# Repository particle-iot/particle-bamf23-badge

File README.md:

# Particle Bay Area Maker Faire 2023 Water Balloon Badge 

## Our interactive game

If you stopped by the Particle booth for the 2023 Bay Area Maker Faire, spun the prize wheel, and were lucky enough to win our badge, we hope you had a blast playing! 

So, how does it work? Participants turn on their badge(s) and wait for the small LED to glow cyan, letting them know it's ready for a game match to begin. The badge has four buttons, each serving as a launcher for virtual water balloons. Each button triggers attacks with varying strengths, all determined by a virtual die roll. Players take turns launching virtual water balloons, and after an attack and counter-attack, the badges will display the result of the match automatically.  The badge lights up green for a win, red for loss, or blue for a draw.  Players engage with fellow attendees in virtual water balloon battles, roll the dice, aim for high-strength attacks, and secure their win!

Players can only battle the same player up to 10 times (after which badges win glow white to alert you of the limit), so everyone must engage with new players to climb up the leaderboard.

Pro Tip: Point the die side edges of the badges towards each other for the best results (like the video below). The max distance is 10 feet, but the closer you are, the better.

Fun fact: iPhone IR depth mapping is detrimental to gameplay functionality.  So if you are wondering why your badges seem camera shy while videoing, this is why :D

## Gameplay

## Behind the Badge

The Photon 2 based badge isn't just a fun toy. With features like a dual-row socket for Photon 2, an ON/OFF switch, lanyard slots, 7 neopixel RGB LEDs, humidity and temperature sensor, QWIIC/Stemma connector, and a speaker, it's also a toolkit for your post-conference projects. The badge's 38kHz IR demodulator and LEDs also ensure efficient communication for the game.

## Hardware

All the parts are described in Bill of Materials [particle-bamf23-badge.csv](hardware/v1.0/pcb/)

OSHPark is a good place to order with purple or the new "after dark" theme color scheme.  You can upload the KiCad [particle-bamf23-badge.kicad_pcb](hardware/v1.0/pcb/) there directly.  I would download this entire Github repo ZIP file first though instead of just trying to save the PCB file from your browser.

Another way to order PCB's is by using the included [gerbers](hardware/v1.0/gerbers/) and uploading those with all of the necessary specs to companies like [PCBWay](https://www.pcbway.com) or [JLCPCB](https://jlcpcb.com)

The cyberdeck is a Raspberry Pi 400 computer, with Pimoroni Hyperpixel 4.0 Square LCD, along with another water balloon badge for input.  The badge is powered and connected to the pi over USB, and takes input on USB serial /dev/ttyACM0.  Everything was mounted to a laser cut acrylic piece that was bent at a nice angle.  The 40-pin cable was a real pain to make, since every pair of wires was twisted to ensure the proper orientation.  I highly suggest buying one of Adafruit's cyberdeck boards instead.

## Software

```
software/v1.0/badge (badge firmware)
software/v1.0/badge-build (badge build directory)
software/v1.0/badge-interface (badge-interface firmware)
software/v1.0/badge-interface-build (badge-interface build directory)
software/v1.0/leaderboard (cyberdeck software)
```

### Compile prerequisites

- Install [Particle CLI](https://docs.particle.io/getting-started/developer-tools/cli/)
- Login to the CLI with your Particle account `particle login`
- Install [Device OS Flash Util](https://github.com/particle-iot/device-os-flash-util)

### Badge

To build the badge firmware, connect a badge over USB and run:

```
cd software/v1.0/badge-build
./build.sh 5.5.0
```

### On-Board SHT31 Temperature/Humidity

To build the SHT31 Temperature/Humidity Demo:

```
change the #define ENABLE_ON_BOARD_SHT31 to (1) at the top of the particle-bamf23-badge.cpp file
cd software/v1.0/badge-build
./build.sh 5.5.0
```

### QWIIC/STEMMA Conenctor Support

To build the QWIIC/STEMMA Conenctor Demo:
I used the VCNL4040 Ambient Light Sensor, but there are tons of sensors to experiment with

```
change the #define ENABLE_QWIIC_SENSOR_DEMO to (1) at the top of the particle-bamf23-badge.cpp file
cd software/v1.0/badge-build
./build.sh 5.5.0
```

### Badge Interface (for Cyberdeck)

To build the badge-interface firmware, connect a badge over USB and run:

```
cd software/v1.0/badge-interface-build
./build.sh 5.5.0
```

### Cyberdeck

To run the cyberdeck software on a Raspberry Pi-400:

```
- copy the cyberdeck folder to your raspberry pi
- ensure node.js is installed ( https://pimylifeup.com/raspberry-pi-nodejs (other seemingly simpler ways didn't work!) )
- ensure electron is installed globally `npm i -g electron`
- run `npm install` the first time to populate all of the libraries
- in one terminal tab run `electron electron.js`
- in another terminal tab run `node server.js`
- Note: this will likely crash without the leaderboard server running as well, accepting score requests.  I'm leaving that part as an excercise for you.  You can use an express app to accomplish this, with some effort :D  Your leaderboard server should use a local MongoDB so you can restart it from time to time without losing the scores and user nicknames collected.  I ended up implementing separate collections for users and game/score data.
```

# License

Creative Commons Attribution-ShareAlike 4.0 International (CC BY-SA 4.0) - essentially do whatever you want, Full [LICENSE here](LICENSE)

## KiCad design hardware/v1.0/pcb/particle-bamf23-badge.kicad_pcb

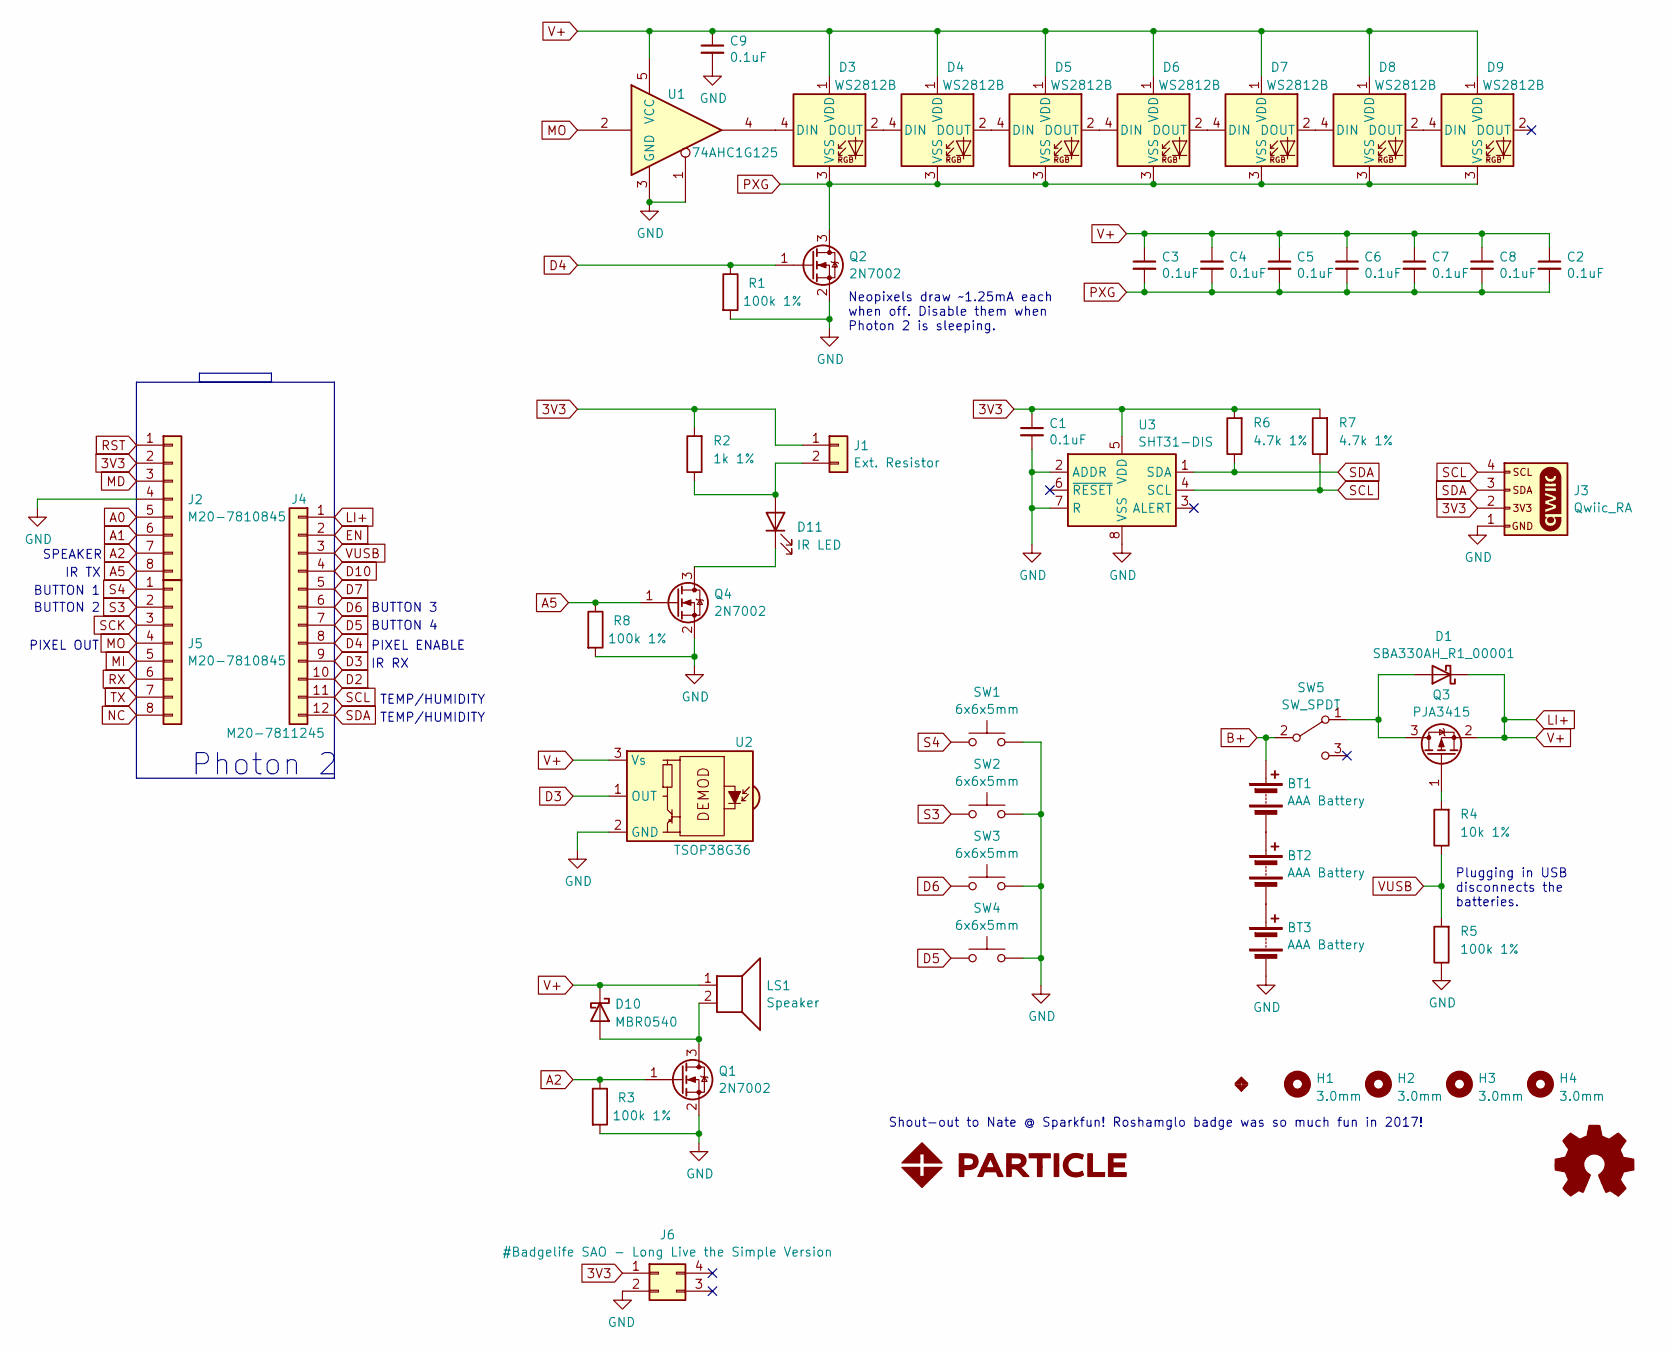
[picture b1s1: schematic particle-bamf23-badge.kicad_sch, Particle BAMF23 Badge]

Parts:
BT1, BT2, BT3: AAA Battery; BatteryHolder_MPD_BK82_AAA
C1, C2, C3, C4, C5, C6, C7, C8, C9: 0.1uF; C_0805_2012Metric_Pad1.20x1.40mm_HandSolder
D1: SBA330AH_R1_00001; D_SOD-123HE
D3, D4, D5, D6, D7, D8, D9: WS2812B; LED_WS2812B_PLCC4_5.0x5.0mm_P3.2mm
D10: MBR0540; D_SOD-123
D11: IR LED; LED_D5.0mm_Horizontal_O1.27mm_Z3.0mm
G1: LOGO; particle-logo-stacked-10mm-sm
G2: LOGO; particle-logo-38mm-ss
H1, H2, H3, H4: 3.0mm; MountingHole_4.0mm_M3.0
J1: Ext. Resistor; PinHeader_1x02_P2.54mm_Vertical
J2, J5: M20-7810845; Harwin_M20-7810845_2x08_P2.54mm_Vertical
J3: Qwiic_RA; JST04_1MM_RA
J4: M20-7811245; Harwin_M20-7811245_2x12_P2.54mm_Vertical
J6: #Badgelife SAO - Long Live the Simple Version; PinHeader_2x02_P2.54mm_Vertical
LS1: Speaker; MagneticBuzzer_FUET-9032-05
Q1, Q2, Q4: 2N7002; SOT-23_HandSoldering
Q3: PJA3415; SOT-23_HandSoldering
R1, R3, R5, R8: 100k 1%; R_0805_2012Metric_Pad1.20x1.40mm_HandSolder
R2: 1k 1%; R_0805_2012Metric_Pad1.20x1.40mm_HandSolder
R4: 10k 1%; R_0805_2012Metric_Pad1.20x1.40mm_HandSolder
R6, R7: 4.7k 1%; R_0805_2012Metric_Pad1.20x1.40mm_HandSolder
SW1, SW2, SW3, SW4: 6x6x5mm; SW_Push_1P1T_NO_6x6mm_H5mm
SW5: SW_SPDT; SW_SPDT_PCM12
U1: 74AHC1G125; SOT-23-5_HandSoldering
U2: TSOP38G36; Vishay_MINICAST-3Pin
U3: SHT31-DIS; Sensirion_DFN-8-1EP_2.5x2.5mm_P0.5mm_EP1.1x1.7mm

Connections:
3V3: C1.1, J1.1, J2.2, J3.2, J6.1, R2.2, R6.2, R7.2, U3.5 (VDD)
A0: J2.5
A1: J2.6
A2: J2.7, Q1.1 (G), R3.1
A5: J2.8, Q4.1 (G), R8.1
B+: BT1.1 (+), SW5.2 (B)
D2: J4.10
D3: J4.9, U2.1 (OUT)
D4: J4.8, Q2.1 (G), R1.1
D5: J4.7, SW4.1
D6: J4.6, SW3.1
D7: J4.5
D10: J4.4
EN: J4.2
GND: BT3.2 (-), C1.2, C9.2, J2.4, J3.1, J6.2, Q1.2 (S), Q2.2 (S), Q4.2 (S), R1.2, R3.2, R5.1, R8.2, SW1.2, SW2.2, SW3.2, SW4.2, U1.1, U1.3 (GND), U2.2 (GND), U3.2 (ADDR), U3.7 (R), U3.8 (VSS), U3.9 (VSS)
LI+: C2.1, C3.1, C4.1, C5.1, C6.1, C7.1, C8.1, C9.1, D1.1 (K), D3.1 (VDD), D4.1 (VDD), D5.1 (VDD), D6.1 (VDD), D7.1 (VDD), D8.1 (VDD), D9.1 (VDD), D10.1 (K), J4.1, LS1.1, Q3.2 (S), U1.5 (VCC), U2.3 (Vs)
MD: J2.3
MI: J5.5
MO: J5.4, U1.2
NC: J5.8
unnamed: BT1.2 (-), BT2.1 (+)
unnamed: BT2.2 (-), BT3.1 (+)
unnamed: D1.2 (A), Q3.3 (D), SW5.1 (A)
unnamed: D3.4 (DIN), U1.4
unnamed: D3.2 (DOUT), D4.4 (DIN)
unnamed: D4.2 (DOUT), D5.4 (DIN)
unnamed: D5.2 (DOUT), D6.4 (DIN)
unnamed: D6.2 (DOUT), D7.4 (DIN)
unnamed: D7.2 (DOUT), D8.4 (DIN)
unnamed: D8.2 (DOUT), D9.4 (DIN)
unnamed: D10.2 (A), LS1.2, Q1.3 (D)
unnamed: D11.2 (A), J1.2, R2.1
unnamed: D11.1 (K), Q4.3 (D)
unnamed: Q3.1 (G), R4.2
PXG: C2.2, C3.2, C4.2, C5.2, C6.2, C7.2, C8.2, D3.3 (VSS), D4.3 (VSS), D5.3 (VSS), D6.3 (VSS), D7.3 (VSS), D8.3 (VSS), D9.3 (VSS), Q2.3 (D)
RST: J2.1
RX: J5.6
S3: J5.2, SW2.1
S4: J5.1, SW1.1
SCK: J5.3
SCL: J3.4, J4.11, R7.1, U3.4 (SCL)
SDA: J3.3, J4.12, R6.1, U3.1 (SDA)
TX: J5.7
VUSB: J4.3, R4.1, R5.2

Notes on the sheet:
Shout-out to Nate @ Sparkfun! Roshamglo badge was so much fun in 2017!
BUTTON 3
BUTTON 4
PIXEL OUT
BUTTON 2
IR TX
Plugging in USB disconnects the batteries.
IR RX
Photon 2
PIXEL ENABLE
Neopixels draw ~1.25mA each when off. Disable them when Photon 2 is sleeping.
SPEAKER
TEMP/HUMIDITY
BUTTON 1

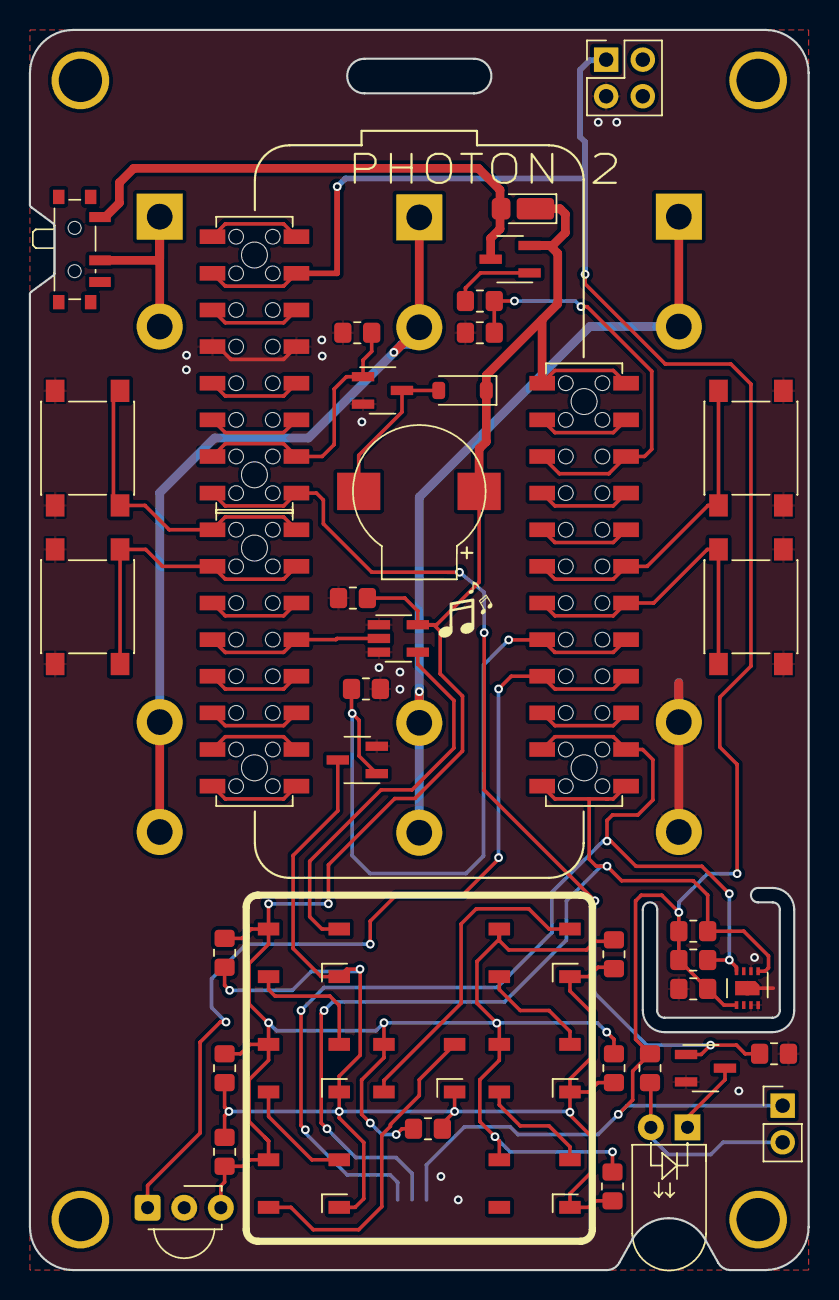
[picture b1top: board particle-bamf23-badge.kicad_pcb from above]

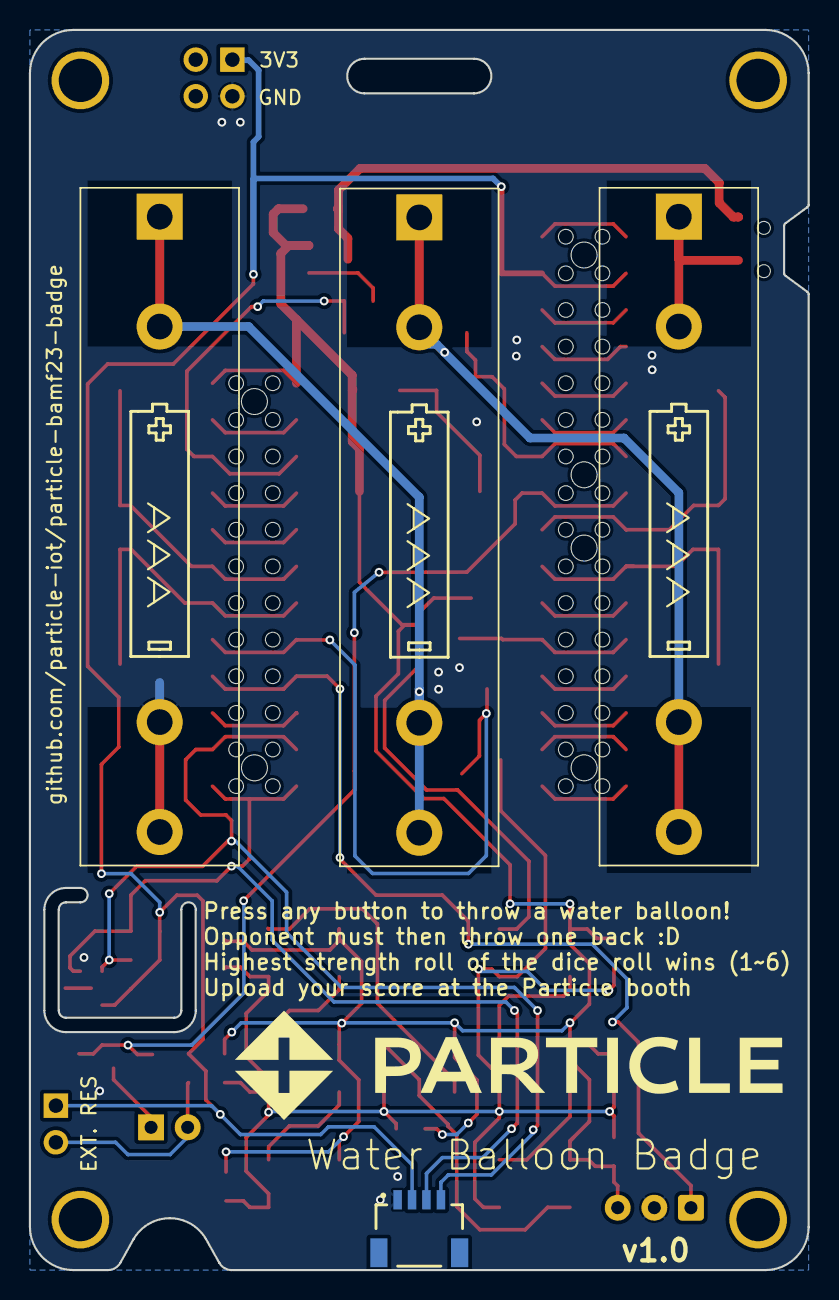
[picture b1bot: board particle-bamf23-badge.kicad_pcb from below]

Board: 2 copper layers, 54.0 x 86.0 mm, 55 parts (5 on the bottom side), 31 nets.

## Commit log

2023-09-04 adds badge pcb v0.1
2023-10-22 adds badge firmware v0.1
2023-10-22 adds badge pcb v1.0
2023-10-22 adds cyberdeck software v1.0
2023-10-22 adds badge-interface firmware v1.0
2023-10-22 adds badge firmware v1.0
